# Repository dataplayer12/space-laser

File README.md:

# Space Laser
Interstellar communications with a laser and arduino

## Basic Idea

Powerful laser beams can penetrate the Earth's atmosphere and travel far into space, providing an effective means of communication for hobbyists and space agencies alike. This project is a hobbyist's attempt to explore the current state of the technology required to send signals into space over interstellar distances. Specifically, I am interested in technology which is available to hobbyists, does not require licences or permits from government agencies to use and costs no more than a hundred US dollars.

----
It has been established by experiments conducted on International Space Station (ISS) that a 1 Watt blue laser beam sent from the surface of the earth not only reaches space, but is powerful enough to be seen by the naked human eye. See Scott Manley's great video on this:  

## Know-how

There are a few things to know about when starting this project. 

### Problem: The danger of lasers

Lasers are extremely dangerous for all kinds of life forms, especially if pointed directly in the eyes. Typically, a laser pointer has a power output of \~1 mW. This power is not enough to send a signal into space (or to blind someone). As mentioned earlier, a laser of power about 1 watt or higher is sufficient although theoretically, we could use a much lower power. A calculation can be made to find the minimum power of the laser such that a certain amount of light escapes into space, given the absorbance characteristics of the earth's atmosphere. Such calculations are straightforward, but are not presented here, since very high power lasers are available online, which means that we are not scratching the bottom of this threshold, even as a hobbyist. However, at such high powers of 1 W or more, the laser is powerful enough to make someone blind instantly if it were pointed directly in their eyes. While it is in use, the laser may get knocked off or pushed by a person, animal or just due to wind or the cable may get yanked off for any number of reasons. All of these could potentially lead to a fatal accident.

### Solution: Motion detection circuit
To make sure that Murphy does not mess things up, I designed a circuit which consists of a MPU 6050 accelerometer and gyroscope and an arduino.
The arduino (basically, an ATMega 328P chip, with arduino bootloader) constantly monitors the reading of the MPU 6050 and if a sudden motion is detected, the laser is instantly shut off.

### Problem: Communication protocol
Supposing that the laser is safe enough to use, the next step is to think about communication. I am specifically focusing on lasers which are meant to be used in CNCs and laser cutters etc. These lasers accept a TTL signal. The output of the laser is adjusted as per the amplitude and frequency characteristics of the TTL signal. So, we can easily modulate the intensity of the laser. The second type of communication we should think about is interstellar. How should we encode the information we are sending, so that a civilization which detects it can decode it?\* 

### Solution: Half-duplex UART protocol
Since the lasers we are using are basically cheap, low quality ones, we cannot encode information in other properties of the light beam such as phase or polarization of even fancier: angular momentum. All we can do is modulate the intensity of the beam. The signal may be very weak when it reaches the receiver, so it is preferable to modulate the intensity in a digital binary pattern, rather than some analog form. So, given that we are using a binary transmitter and the receiver would not understand what the heck is being transmitted, we should use a protocol that is as simple as possible to decode. The simplicity and robustness of the UART protocol makes it ideal for use in such communication. The protocol contains a start and stop bit and encodes the byte within these two (we consider the case without any parity bits). Thus, anyone looking at a binary pattern of UART signals would notice the periodicity and that the data between the two start/stop bits varies. Thus, I expect that a completely alien civilization can establish the concept of data packet used in UART protocol. The next detail to consider is the baud rate. CNC/cutting lasers I found on the internet would typically have a maximum modulation frequency of 10KHz to 20 KHz. The one I am using advertises 20 KHz, but I have no way to verify this. To be safe, I used a baud rate of 9600. This is extremely slow, but I expect that most lasers can keep up with this baud rate. Finally, a minor detail is that this communication will be half-duplex, meaning that we will not be receiving any data from the aliens. If you can improve upon this project to establish a full-duplex comm channel with aliens, please let me know.

\*The odds of some civilization intercepting our signal are astronomically small, but that's a minor detail for optimists.

### Problem: Mechanical stability
Even if a safety circuit (basically the MPU sensor) is installed, we still need to make sure that it faithfully represents the true motion of the laser. For that, the circuit needs to be mechanically rigidly attached to the laser. There are two problems associated with this. First, all good high-power lasers have fans, which are constantly running. This presents a large source of noise for the sensor since the fan is attached directly to the laser. Second, even with the fan attached, the laser gets quite hot. Thus, it is not advisable to attach the motion detection circuit directly to the laser since that would block the airflow from the laser and also potentially damage the motion detection circuit. These are small problems by comparison.

### Solution: 3D printed mount
The solution is to mechanically isolate the (laser+fan) from the circuit enough to attenuate the vibrations from the fan but still be bind the circuit to the laser rigidly. This requires an adapter. So, I designed an adapter which accommodates both the laser and the circuit, but isolates them enough so that vibrations from the fan do not overwhelm the MPU 6050. The residual vibration from the fans can be measured and a threshold can be set in the code, so that fan vibrations are ignored.

## Strategy
If you decide to build this project, some specific details of your may differ from mine, so I am outlining the basic steps I performed to get everything working.

- Buy a powerful laser online. I got mine from Amazon It has a wavelength of 445 nm (blue color) and maximum average output power of **5.5 Watts** (or 5000 times that of a laser pointer)
- Build a circuit on breadboard to test the performance of MPU 6050.
- Write code for arduino performing safety check.
- Write code to send data from computer to laser.
- Design a PCB to emulate the breadboard design. This makes sure that the circuit is robust and there are no hanging wires as in a breadboard.

I ended up using two ATMega chips: one for minitoring the motion and one for communication with the computer over bluetooth (with a HC-05 bluetooth module). Thus, my PCB design has two chips. This is done so that there is as little lag as possible between the detection of motion and halting of the laser output. This is just a precaution on my part. It is okay to let one chip handle both these tasks if you are confident that no matter what your code will halt the laser within some acceptable latency.

## Circuit
Here is what my PCB looks like.

The PCB design files are in `pcb` directory in Eagle format. The gerber files are in a `zip` file and can be uploaded to your PCB provider's website to be manufactured. I ordered mine from JLCPCB.

## Holder
Here is the 3D design for the holder. The base holds the laser using the M3 size mounting holes while the pillars hold the PCB (also via M3 screws). The center of the base has mounting hole for a quarter-inch tripod screw. So, the whole laser assmebly can be mounted on a tripod, making it easier to aim the beam anywhere.

The STL file is in the `holder` directory. I printed the holder with PLA using typical parameters for this material at 15% infill on a FlashForge printer.

## Code
- The code for the two arduinos is in `laser_safety` and `laser_transmitter` directories.
- The script `stream_live_video.py` can be used to transmit pictures taken from the webcam on your computer to the laser (using a bluetooth module). Since we are using a baud rate of 9600, we can't transmit the video in real time, but it's kind of cool to stream snapshots of your weekend party into outer space.
- The directory `mindwave` contains some experimental scripts to send EEG data (brain waves) from a NeuroSky Mindwave 2 to the laser. This allows you to attach an EEG reader to your head and transmit your brain waves into outer space! This part of the project is still under development.

## Results
It works!

### Hailing the Chandrayaan-2 lander
Here I am sending a sentence "Hello Vikram! Please respond" to the approximate location where India's Chandrayaan-2 moon mission hard-landed. It did not respond.

### Sending a selfie to betelgeuse
Betelgeuse is an extremely interesting star. There are probably no planets around betelgeuse and almost certainly no intelligent life, but this maverick star could go supernova in the ≈600 years that it takes light to reach there from Earth. Even if it doesn't, it's kind of cool to have your selfie zip through a massive star. It is possible that the large gravitational effect of the star will cause the laser light to bend around it and go somewhere else. Now that I think about it, it would be interesting to calculate the effect that betelgeuse's gravitational field would have on the timing of the UART signals being sent. I will do that calculation once I learn general relativity.

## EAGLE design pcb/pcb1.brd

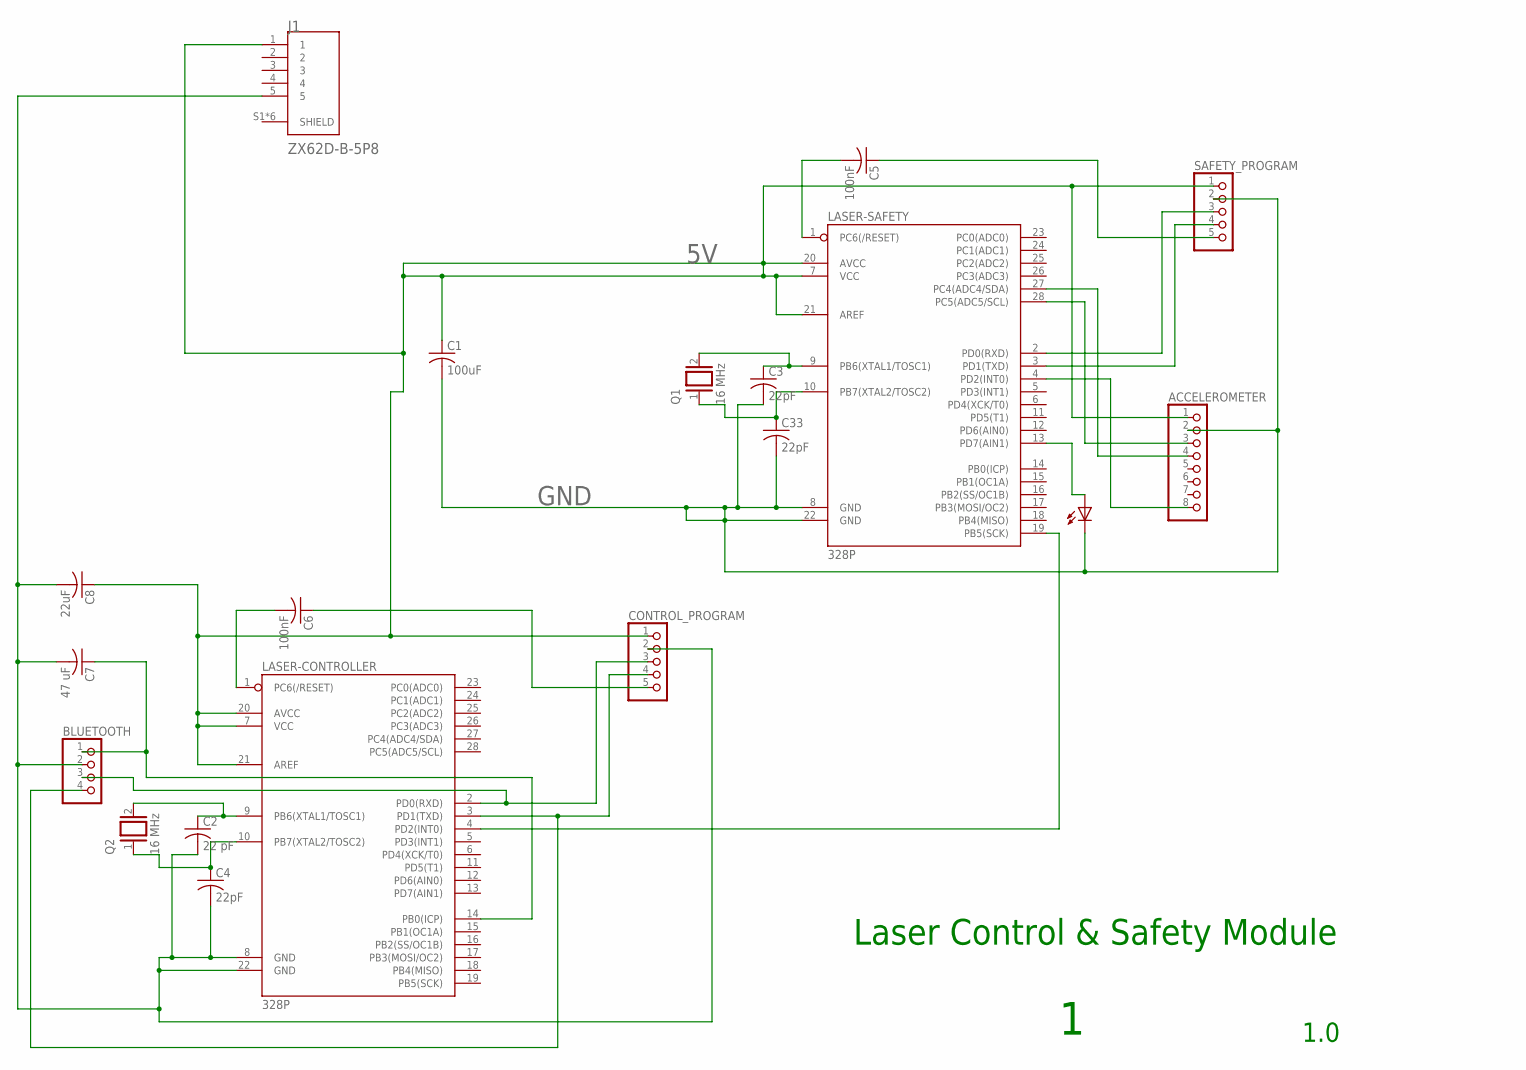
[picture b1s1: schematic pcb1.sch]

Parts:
ACCELEROMETER: PINHD-1X8; 1X08
BLUETOOTH: PINHD-1X4; 1X04
C1: 100uF; C025-030X050
C2: 22 pF; C025-025X050
C3, C4, C33: 22pF; C025-025X050
C5, C6: 100nF; C025-025X050
C7: 47 uF; C025-024X044
C8: 22uF; C025-024X044
CONTROL_PROGRAM: PINHD-1X5; 1X05
J1: ZX62D-B-5P8; HRS_ZX62D-B-5P8
LASER-CONTROLLER: 328P; DIP28
LASER-SAFETY: 328P; DIP28
Q1, Q2: 16 MHz; QS
SAFETY_PROGRAM: PINHD-1X5; 1X05
U$1: LEDLED3MM; LED3MM

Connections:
5V: ACCELEROMETER.1, C1.1, C8.1, CONTROL_PROGRAM.1, J1.1, LASER-CONTROLLER.7 (VCC), LASER-CONTROLLER.20 (AVCC), LASER-CONTROLLER.21 (AREF), LASER-SAFETY.7 (VCC), LASER-SAFETY.20 (AVCC), LASER-SAFETY.21 (AREF), SAFETY_PROGRAM.1
GND: ACCELEROMETER.2, BLUETOOTH.2, C1.2, C2.2, C3.2, C4.2, C7.2, C8.2, C33.2, CONTROL_PROGRAM.2, J1.5, LASER-CONTROLLER.8 (GND), LASER-CONTROLLER.22 (GND), LASER-SAFETY.8 (GND), LASER-SAFETY.22 (GND), SAFETY_PROGRAM.2, U$1.K (C)
unnamed: C4.1, LASER-CONTROLLER.10 (PB7(XTAL2/TOSC2)), Q2.1
unnamed: LASER-SAFETY.13 (PD7(AIN1)), U$1.A
unnamed: LASER-CONTROLLER.4 (PD2(INT0)), LASER-SAFETY.19 (PB5(SCK))
unnamed: C5.1, SAFETY_PROGRAM.5
unnamed: C5.2, LASER-SAFETY.1 (PC6(/RESET))
unnamed: C2.1, LASER-CONTROLLER.9 (PB6(XTAL1/TOSC1)), Q2.2
unnamed: BLUETOOTH.3, CONTROL_PROGRAM.3, LASER-CONTROLLER.2 (PD0(RXD))
unnamed: BLUETOOTH.4, CONTROL_PROGRAM.4, LASER-CONTROLLER.3 (PD1(TXD))
unnamed: C6.1, CONTROL_PROGRAM.5
unnamed: C6.2, LASER-CONTROLLER.1 (PC6(/RESET))
unnamed: ACCELEROMETER.3, LASER-SAFETY.28 (PC5(ADC5/SCL))
unnamed: ACCELEROMETER.4, LASER-SAFETY.27 (PC4(ADC4/SDA))
unnamed: ACCELEROMETER.8, LASER-SAFETY.4 (PD2(INT0))
unnamed: BLUETOOTH.1, C7.1, LASER-CONTROLLER.14 (PB0(ICP))
unnamed: LASER-SAFETY.2 (PD0(RXD)), SAFETY_PROGRAM.3
unnamed: C33.1, LASER-SAFETY.10 (PB7(XTAL2/TOSC2)), Q1.1
unnamed: C3.1, LASER-SAFETY.9 (PB6(XTAL1/TOSC1)), Q1.2
unnamed: LASER-SAFETY.3 (PD1(TXD)), SAFETY_PROGRAM.4

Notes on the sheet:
Laser Control & Safety Module
1.0

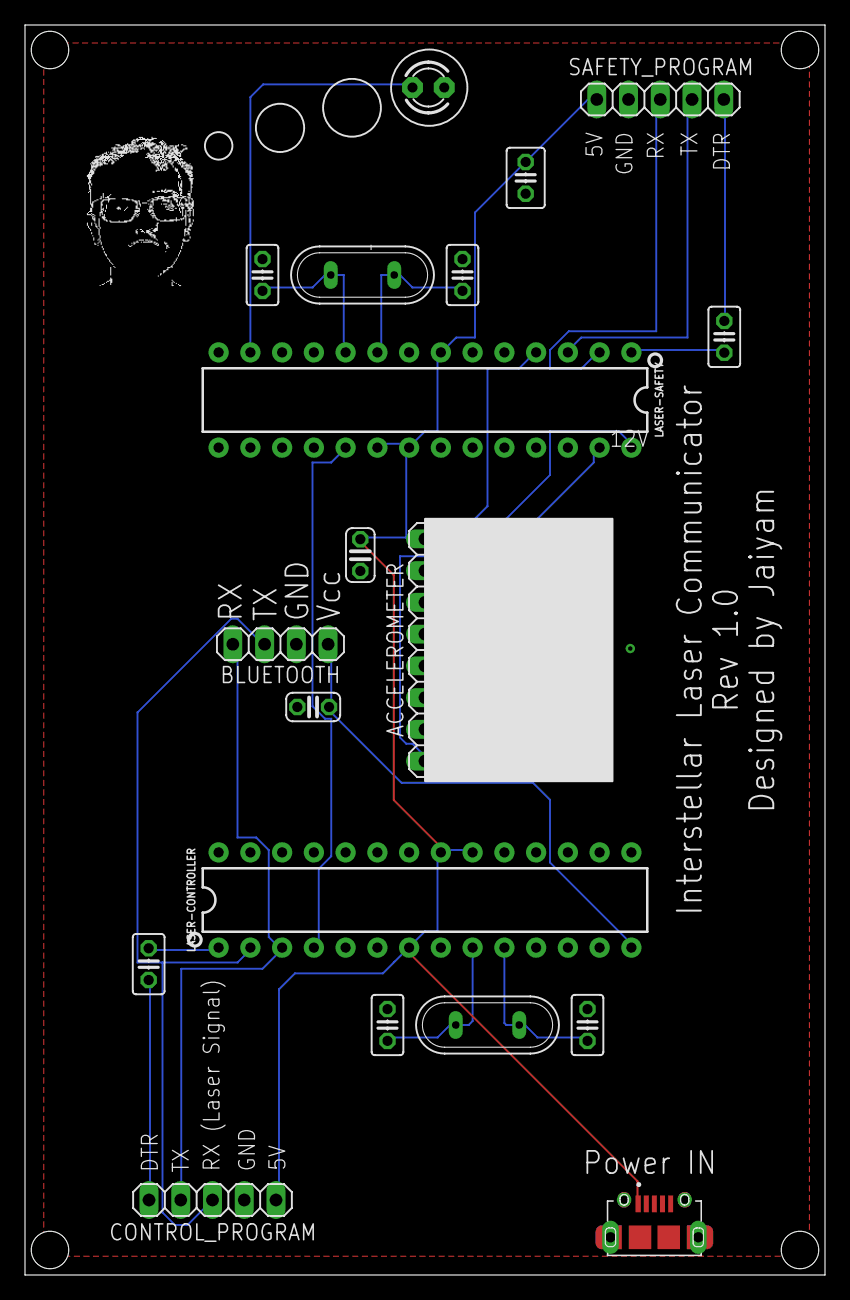
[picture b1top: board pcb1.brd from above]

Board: 2 copper layers, 64.0 x 100.0 mm, 19 parts (0 on the bottom side), 20 nets.

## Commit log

2019-09-27 added arduino scripts
2019-09-27 added pcb design files
2019-09-27 added images of PCB
2019-09-28 added mindwave code, currently not working
2020-04-21 bit-banging safety response
2020-04-21 utilities for streaming video and EEG data
2020-04-21 updated project status
2020-04-22 added holder design
2020-04-22 spell error fix
2020-04-22 small fixes
2020-04-24 improved script

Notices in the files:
parts and their libraries:
SparkFun-IC-Microcontroller: Licensing: Creative Commons ShareAlike 4.0 International - https://creativecommons.org/licenses/by-sa/4.0
